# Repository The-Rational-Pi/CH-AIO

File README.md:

# CH-AIO
 All in one controller for Clone Hero
 
At a minimum, you'll need [OpenSCAD](https://openscad.org/) for the guitar model and [KiCAD](https://www.kicad.org/) for the PCBs.

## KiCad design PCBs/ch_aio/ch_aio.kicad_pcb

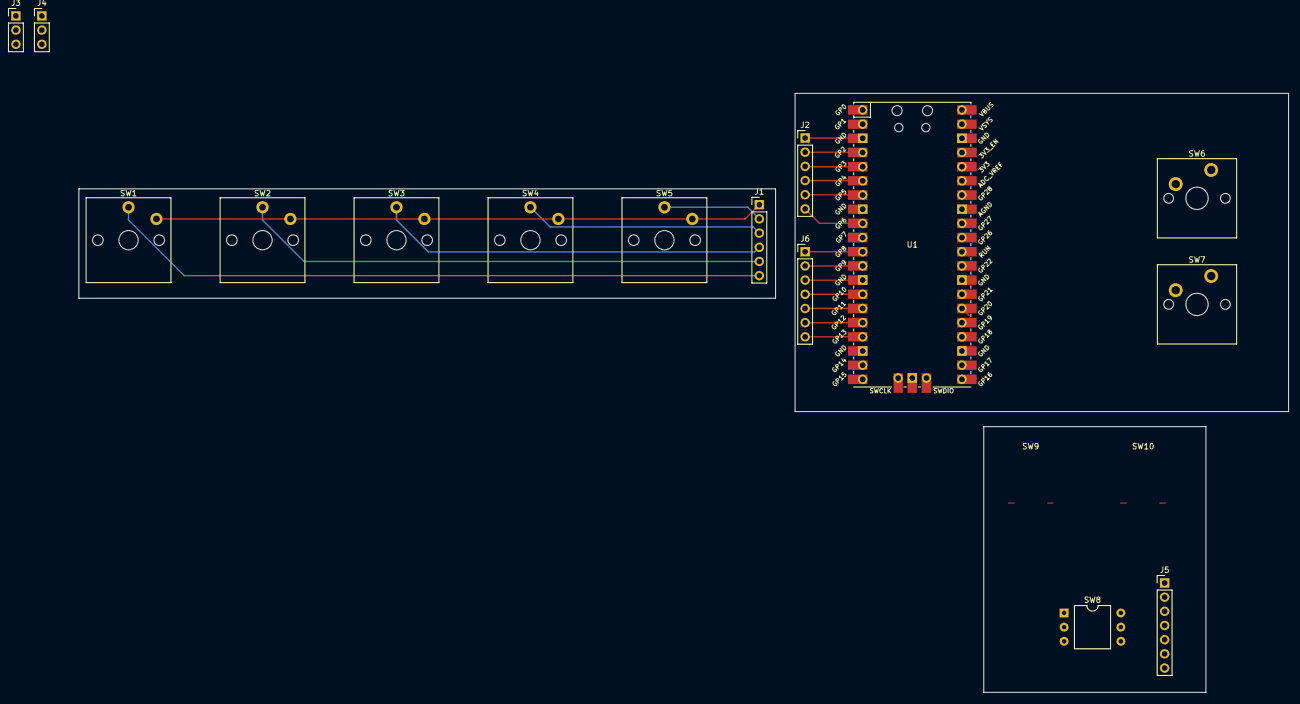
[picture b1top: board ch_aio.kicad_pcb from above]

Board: 2 copper layers, 216.7 x 107.3 mm, 17 parts (0 on the bottom side), 14 nets.

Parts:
J1, J2: Frets; PinHeader_1x06_P2.54mm_Vertical
J3, J4: Strum; PinHeader_1x03_P2.54mm_Vertical
J5, J6: Dpad_start_select; PinHeader_1x07_P2.54mm_Vertical
SW1: Green; SW_Kailh_Choc_V1
SW2: Red; SW_Kailh_Choc_V1
SW3: Yellow; SW_Kailh_Choc_V1
SW4: Blue; SW_Kailh_Choc_V1
SW5: Orange; SW_Kailh_Choc_V1
SW6: Strum_down; SW_Cherry_MX_PCB_1.00u
SW7: Strum_up; SW_Cherry_MX_PCB_1.00u
SW8: hat_5way; DIP-6_W10.16mm
SW9: Start; button_trace
SW10: Select; button_trace
U1: Pico; RPi_Pico_SMD_TH

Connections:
/Blue: J1.3, J2.3, SW4.1, U1.5 (GPIO3)
/Down: J5.5, J6.5, SW8.3 (Down), U1.15 (GPIO11)
/Green: J1.6, J2.6, SW1.1, U1.9 (GPIO6)
/Left: J5.6, J6.6, SW8.4 (Left), U1.16 (GPIO12)
/Orange: J1.2, J2.2, SW5.1, U1.4 (GPIO2)
/Red: J1.5, J2.5, SW2.1, U1.7 (GPIO5)
/Right: J5.7, J6.7, SW8.5 (Right), U1.17 (GPIO13)
/Select: J5.2, J6.2, U1.12 (GPIO9)
/Start: J5.1, J6.1, U1.11 (GPIO8)
/Strum_down: J3.3, J4.3, SW6.1, U1.26 (GPIO20)
/Strum_up: J3.2, J4.2, SW7.1, U1.27 (GPIO21)
/Up: J5.4, J6.4, SW8.2 (Up), U1.14 (GPIO10)
/Yellow: J1.4, J2.4, SW3.1, U1.6 (GPIO4)
GND: J1.1, J2.1, J3.1, J4.1, J5.3, J6.3, SW1.2, SW2.2, SW3.2, SW4.2, SW5.2, SW6.2, SW7.2, SW8.1 (GND), U1.3 (GND), U1.13 (GND), U1.18 (GND), U1.23 (GND), U1.28 (GND), U1.38 (GND), U1.42 (GND)

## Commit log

2022-07-10 Organising
2022-07-11 Move explorer such that strum bar is [0,0]
2022-08-13 Scale Guitar by 10
    why in gods name was I working in cm that whole time
    also made a test switch mount for the fret pcb
2022-08-14 Whammy bar bracket (untested)
2022-08-14 Fixed spring holder, added STLs
2022-08-14 Thinned the bits that slot into the body
2022-08-14 plate width reduction
2022-08-14 front plate inner diameter increase
2022-08-16 "compliant" whammy return mechanism
